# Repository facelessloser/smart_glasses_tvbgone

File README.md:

# smart_glasses_tvbgone
smart_glasses_tvbgone

Blog post - https://facelesstech.wordpress.com/2019/10/26/smart-glasses-tv-b-gone-edition/
Youtube - https://youtu.be/uTr4NMkTZnI

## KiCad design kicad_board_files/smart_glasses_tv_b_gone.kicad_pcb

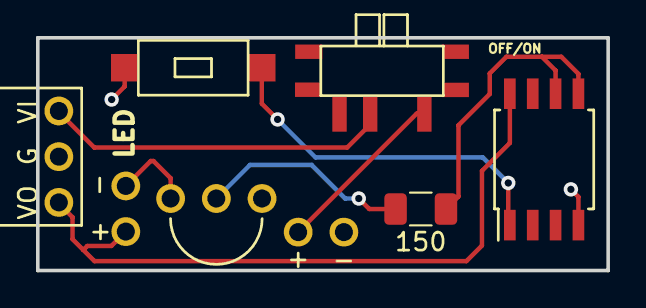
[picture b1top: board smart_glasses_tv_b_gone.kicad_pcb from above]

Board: 2 copper layers, 31.7 x 12.9 mm, 8 parts (0 on the bottom side), 8 nets.

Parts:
150: R; R_1206_3216Metric
D1: LED; through_hole_led
Q1: 2N3055; 2n2222
SW1: SW_DIP_x01; tiny_smd_slide_switch_custom
SW2: SW_Push; SMD_2pin_button_custom
U1: ATtiny85-20SU; SOIJ-8_5.3x5.3mm_P1.27mm
U2: tiny_boost_custom; Tiny_boost_orange
U4: battery_custom; battery_connector_custom

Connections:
unnamed: D1.1, Q1.3
unnamed: D1.2, U1.8, U2.3
unnamed: 150.2, Q1.1
unnamed: Q1.2, SW2.2, U1.4, U2.2, U4.1
unnamed: 150.1, U1.5, U1.6
unnamed: SW1.1, U4.2
unnamed: SW1.2, U2.1
unnamed: SW2.1, U1.1

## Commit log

2019-10-22 board files
2020-02-27 added links to readme
